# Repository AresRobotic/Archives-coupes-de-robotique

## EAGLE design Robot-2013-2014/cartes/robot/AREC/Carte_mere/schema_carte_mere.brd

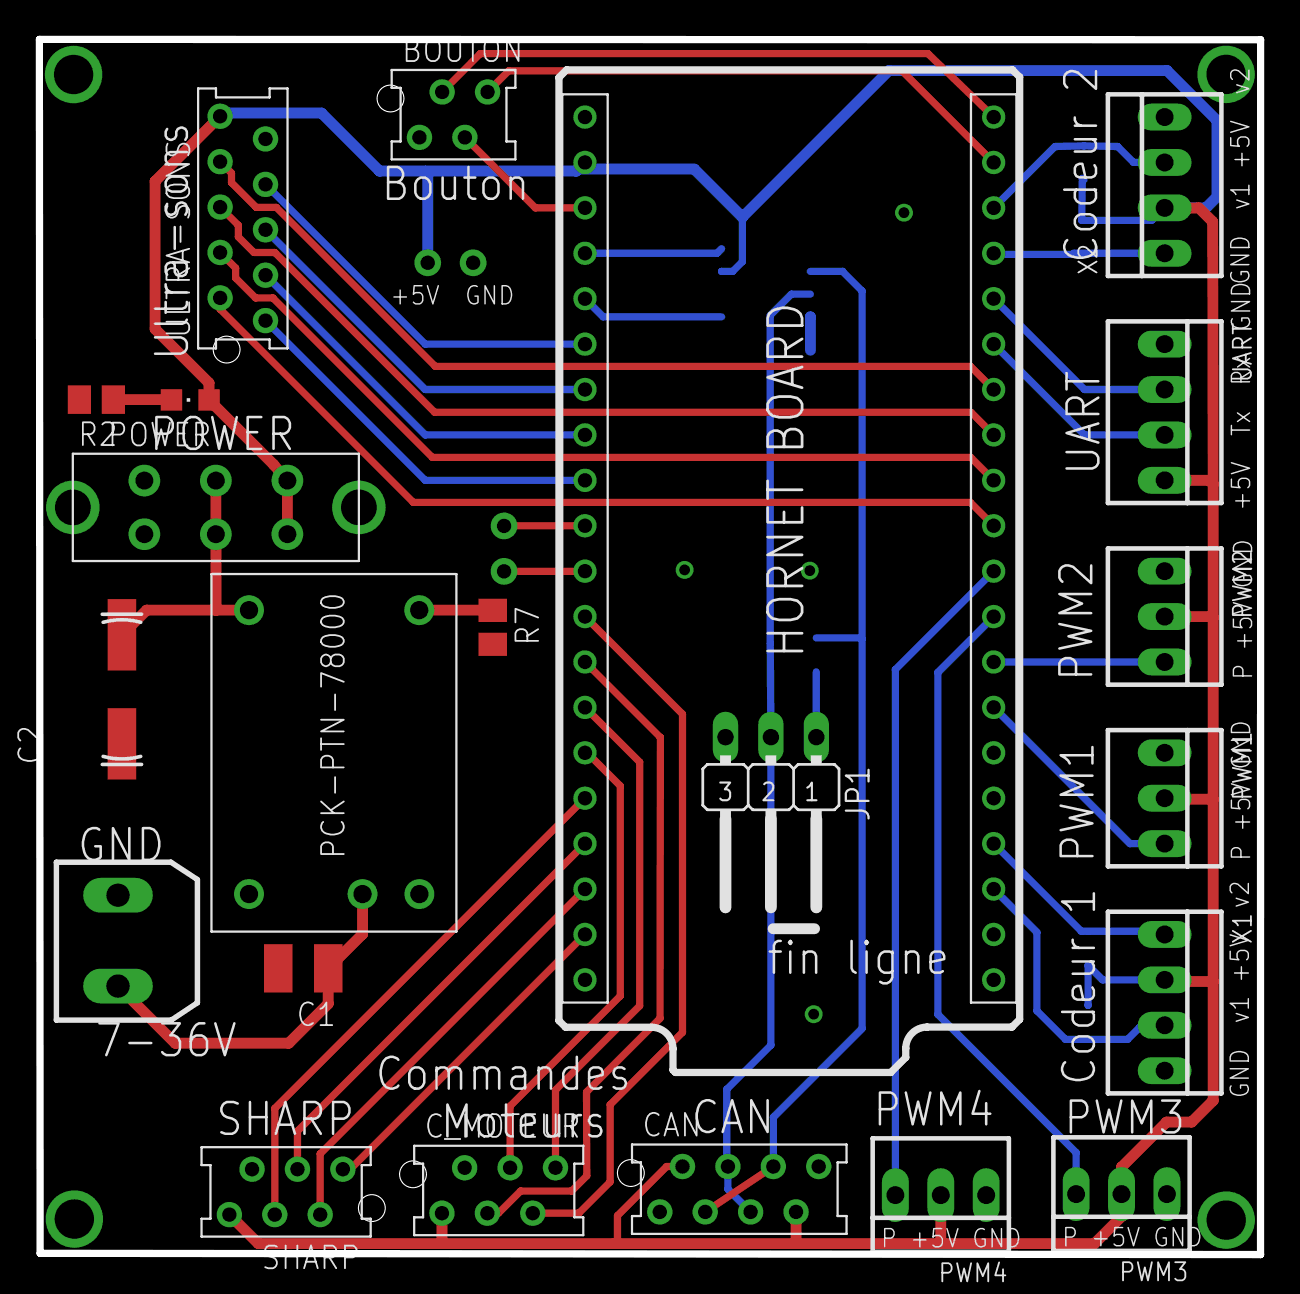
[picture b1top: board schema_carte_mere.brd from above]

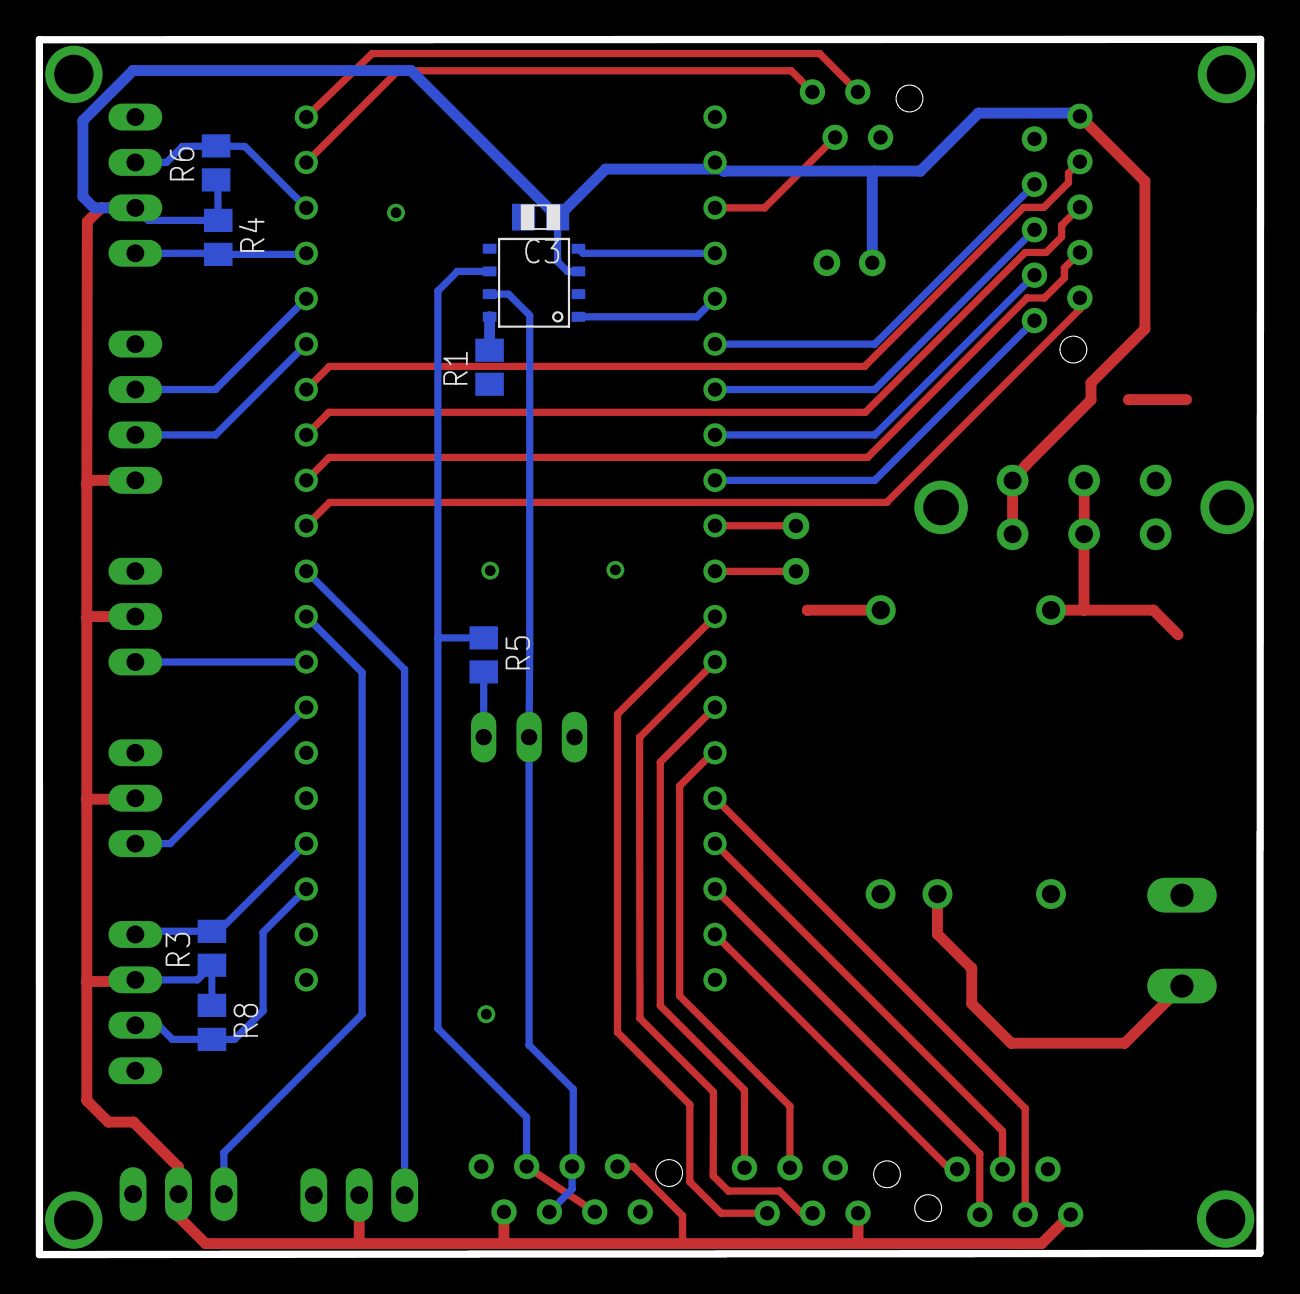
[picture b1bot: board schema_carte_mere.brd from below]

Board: 2 copper layers, 68.3 x 68.0 mm, 32 parts (8 on the bottom side), 43 nets.

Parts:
ALIM: PM5.08_2
BOUTON: MMATCH-4-; AMP-215079-4
C1: 2.2u; C1210
C2: 100uF; 153CLV-0807
C3: 100nF; C0805
CAN: AMP-215079-8
C_MOTEUR: MMATCH-6-; AMP-215079-6
JP1: JP2W
PIN_ALIM: 2_PIN
POWER: CHIPLED_0805
PWM1, PWM2, PWM3, PWM4: 22-23-2031
R1, R7: 21k; M0805
R2: 1k; M0805
R3, R4, R6, R8: 2.7k; M0805
R5: 120; M0805
SHARP: MMATCH-6-; AMP-215079-6
U$1: HORNET_BOARD; HORNET_EXT_20
U$2: MCP2551; SOIC_8
U$3: 2_PIN
U$6: SWITCH
U$18: PTN-78000WAH; PCK-PTN-78000WAH
UART: 22-23-2041
ULTRA-SONS: AMP-215079-10
X1, X2: 22-23-2041

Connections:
+3V3: BOUTON.3, U$1.P$3
+5V: C3.1, CAN.2, CAN.7, C_MOTEUR.1, PIN_ALIM.P$1, POWER.A, PWM1.2, PWM2.2, PWM3.2, PWM4.2, R3.1, R4.1, R6.1, R8.1, SHARP.6, U$1.P$2, U$2.P3, U$6.3, U$6.6, UART.4, ULTRA-SONS.10, X1.2, X2.2
CANH: CAN.4, CAN.5, JP1.2, U$2.P7
CANL: CAN.3, CAN.6, R5.1, U$2.P6
CANRX: U$1.P$4, U$2.P4
CANTX: U$1.P$5, U$2.P1
CODEUR1_V1: R8.2, U$1.P$23, X1.3
CODEUR1_V2: R3.2, U$1.P$24, X1.1
CODEUR2_V1: R4.2, U$1.P$37, X2.1
CODEUR2_V2: R6.2, U$1.P$38, X2.3
COULEUR: BOUTON.4, U$1.P$39
DIR1: C_MOTEUR.3, U$1.P$13
DIR2: C_MOTEUR.5, U$1.P$12
E1: U$1.P$6, ULTRA-SONS.7
E2: U$1.P$7, ULTRA-SONS.5
E3: U$1.P$8, ULTRA-SONS.3
E4: U$1.P$9, ULTRA-SONS.1
GND: ALIM.P$2, BOUTON.1, C1.2, C2.-, C3.2, CAN.1, CAN.8, C_MOTEUR.2, PIN_ALIM.P$2, PWM1.1, PWM2.1, PWM3.1, PWM4.1, R1.1, R2.2, R7.2, SHARP.5, U$1.P$1, U$2.P2, U$18.1, UART.1, ULTRA-SONS.9, X1.4, X2.4
unnamed: ALIM.P$1, C1.1, U$18.2
unnamed: POWER.C, R2.1
unnamed: R1.2, U$2.P8
unnamed: C2.+, U$6.2, U$6.5, U$18.5
unnamed: U$1.P$11, U$3.P$1
unnamed: R7.1, U$18.4
unnamed: JP1.1, R5.2
unnamed: U$1.P$10, U$3.P$2
PWM1: PWM1.3, U$1.P$27
PWM2: PWM2.3, U$1.P$28
PWM3: PWM3.3, U$1.P$29
PWM4: PWM4.3, U$1.P$30
PWM_MOT1: C_MOTEUR.4, U$1.P$15
PWM_MOT2: C_MOTEUR.6, U$1.P$14
SHARP1: SHARP.4, U$1.P$16
SHARP2: SHARP.3, U$1.P$17
SHARP3: SHARP.2, U$1.P$18
SHARP4: SHARP.1, U$1.P$19
T1: U$1.P$34, ULTRA-SONS.8
T2: U$1.P$33, ULTRA-SONS.6
T3: U$1.P$32, ULTRA-SONS.4
T4: U$1.P$31, ULTRA-SONS.2
TIRETTE: BOUTON.2, U$1.P$40
UART_RX: U$1.P$36, UART.2
UART_TX: U$1.P$35, UART.3

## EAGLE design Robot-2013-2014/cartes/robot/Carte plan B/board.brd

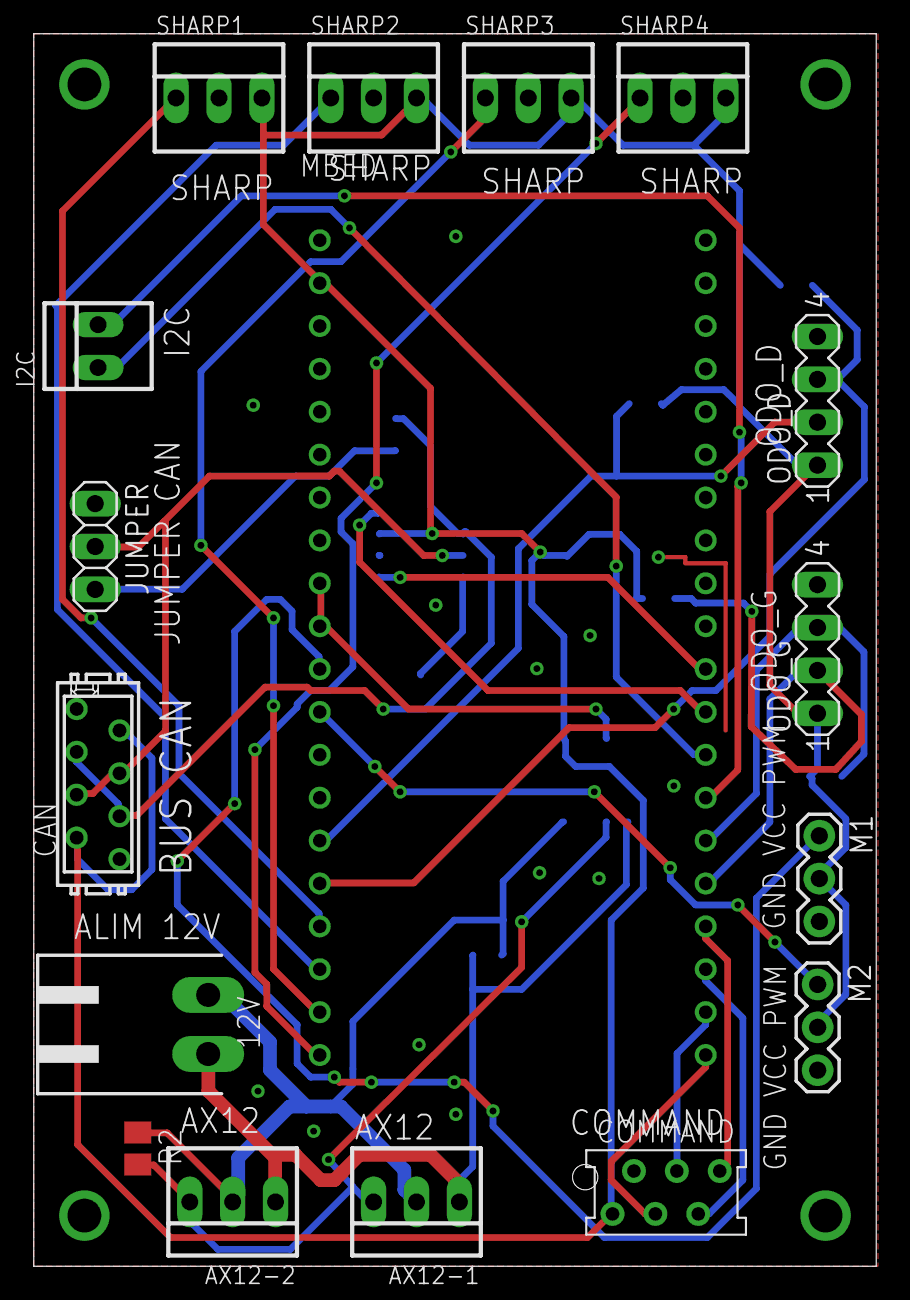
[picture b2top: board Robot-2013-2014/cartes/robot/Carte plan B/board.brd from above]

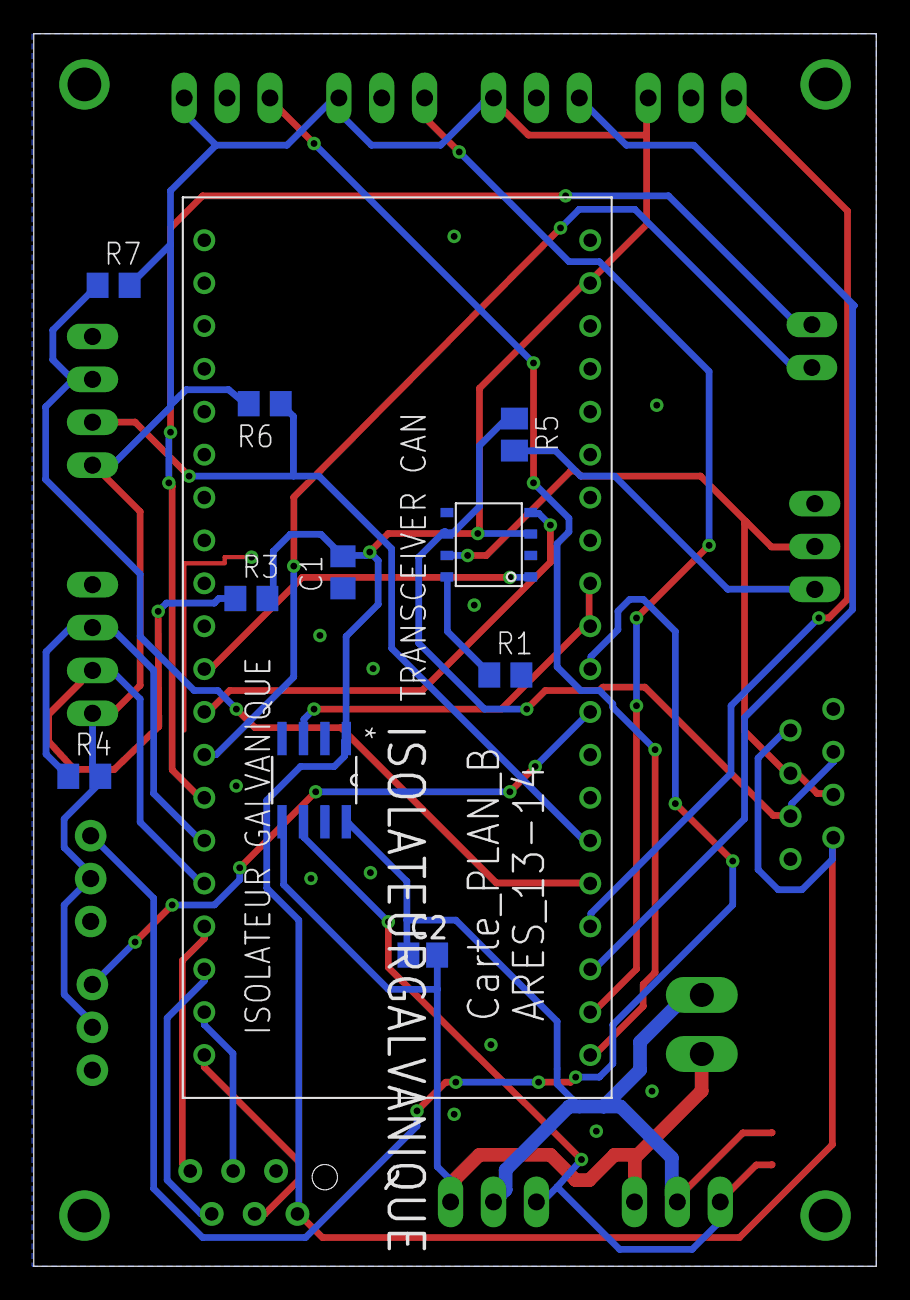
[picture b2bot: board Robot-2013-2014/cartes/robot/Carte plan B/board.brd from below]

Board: 2 copper layers, 49.9 x 73.0 mm, 27 parts (10 on the bottom side), 28 nets.

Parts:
12V: WEIDMULLER 2; 90G-2
AX12-1, AX12-2: molex-3; 22-23-2031
C1: 100n; C0805
C2: 100u; 0805
CAN: micromatch-8; MICROMATCH-8
COMMAND: MMATCH-6-; AMP-215079-6
I2C: header-2; 22-23-2021
ISOLATEURGALVANIQUE: ADUM1250ARZ; SOIC127P600X175-8N
JUMPER: 1X03
M1, M2: SMALL_SERVO; 1X03
MBED: MBED_NXP_LPC1768; MBED-KIT
ODO_D: header-4; MA04-1
ODO_G: header-4; MA04-1
R1: 21k; R0805
R2, R5: 120; M0805
R3, R4, R6, R7: 2,7k; R0805
SHARP1, SHARP2, SHARP3, SHARP4: header-3; 22-23-2031
TRANSCEIVER: MCP2551; SOIC_8

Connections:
+5V: C1.2, CAN.2, CAN.7, COMMAND.1, ISOLATEURGALVANIQUE.1, M1.2, M2.2, MBED.VIN, ODO_D.1, ODO_G.1, R3.2, R4.2, R6.2, R7.2, SHARP1.3, SHARP2.3, SHARP3.3, SHARP4.3, TRANSCEIVER.P3
+12V_DIRTY: 12V.1, AX12-1.2, AX12-2.2, C2.1, ISOLATEURGALVANIQUE.8, R2.1
CANH: CAN.4, CAN.5, JUMPER.2, TRANSCEIVER.P7
CANL: CAN.3, CAN.6, R5.1, TRANSCEIVER.P6
CAN_RX: MBED.P$29, TRANSCEIVER.P4
CAN_TX: MBED.P$30, TRANSCEIVER.P1
CHA_D: MBED.P$15, ODO_D.2, R6.1
CHA_G: MBED.P$25, ODO_G.2, R3.1
CHB_D: MBED.P$16, ODO_D.3, R7.1
CHB_G: MBED.P$26, ODO_G.3, R4.1
DATA_AX12: ISOLATEURGALVANIQUE.3, MBED.P$9, MBED.P$10
DATA_AX12_DIRTY: AX12-1.3, AX12-2.3, ISOLATEURGALVANIQUE.6, R2.2
DATA_SHARP_1: MBED.P$17, SHARP1.1
DATA_SHARP_2: MBED.P$18, SHARP2.1
DATA_SHARP_3: MBED.P$19, SHARP3.1
DATA_SHARP_4: MBED.P$20, SHARP4.1
DIR1: COMMAND.3, MBED.P$21
DIR2: COMMAND.5, MBED.P$23
GND: C1.1, CAN.1, CAN.8, COMMAND.2, ISOLATEURGALVANIQUE.4, M1.3, M2.3, MBED.GND, ODO_D.4, ODO_G.4, R1.2, SHARP1.2, SHARP2.2, SHARP3.2, SHARP4.2, TRANSCEIVER.P2
GND_DIRTY: 12V.2, AX12-1.1, AX12-2.1, C2.2, ISOLATEURGALVANIQUE.5
I2C_SCL: I2C.2, MBED.P$27
I2C_SDA: I2C.1, MBED.P$28
unnamed: R1.1, TRANSCEIVER.P8
unnamed: JUMPER.3, R5.2
PWM1: M1.1, MBED.P$11
PWM2: M2.1, MBED.P$12
PWM_MOT1: COMMAND.4, MBED.P$22
PWM_MOT2: COMMAND.6, MBED.P$24

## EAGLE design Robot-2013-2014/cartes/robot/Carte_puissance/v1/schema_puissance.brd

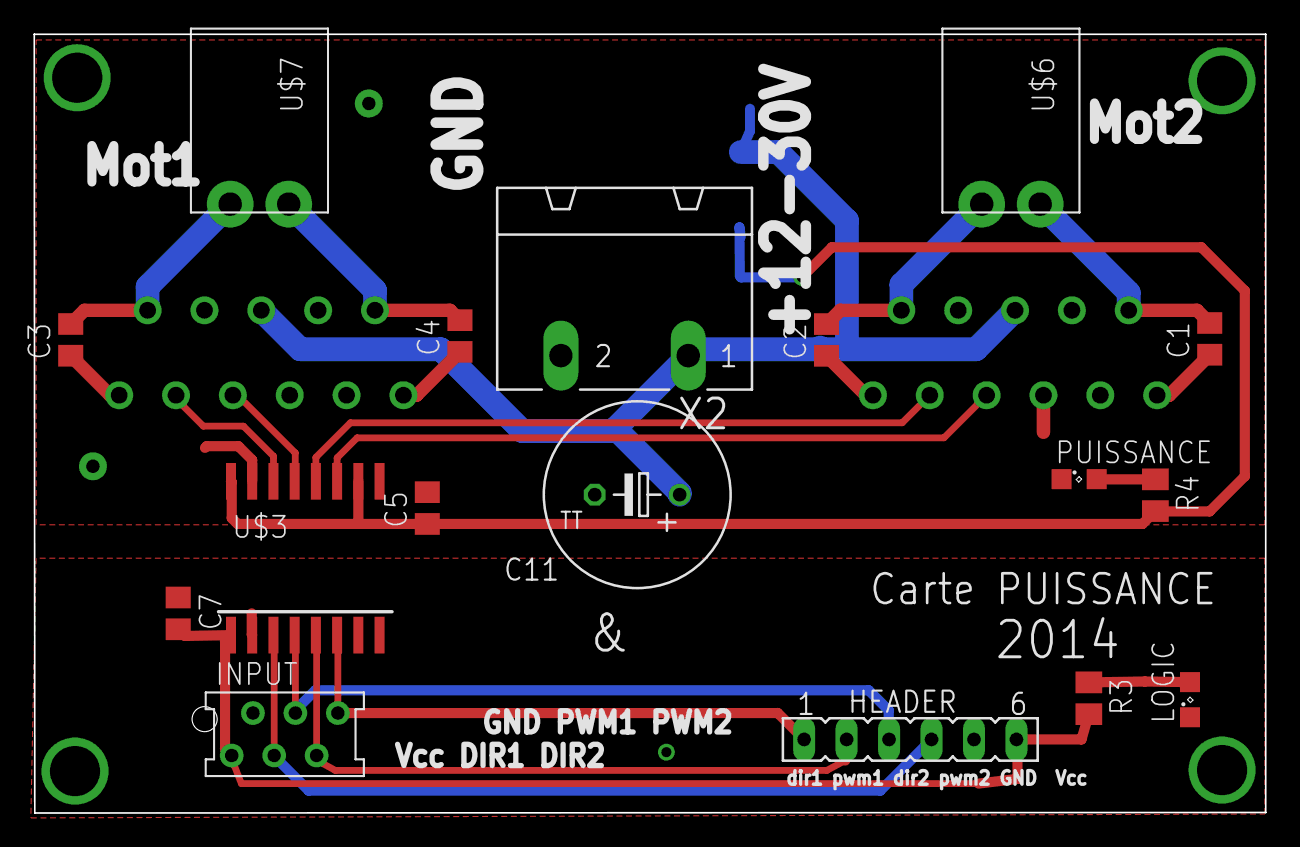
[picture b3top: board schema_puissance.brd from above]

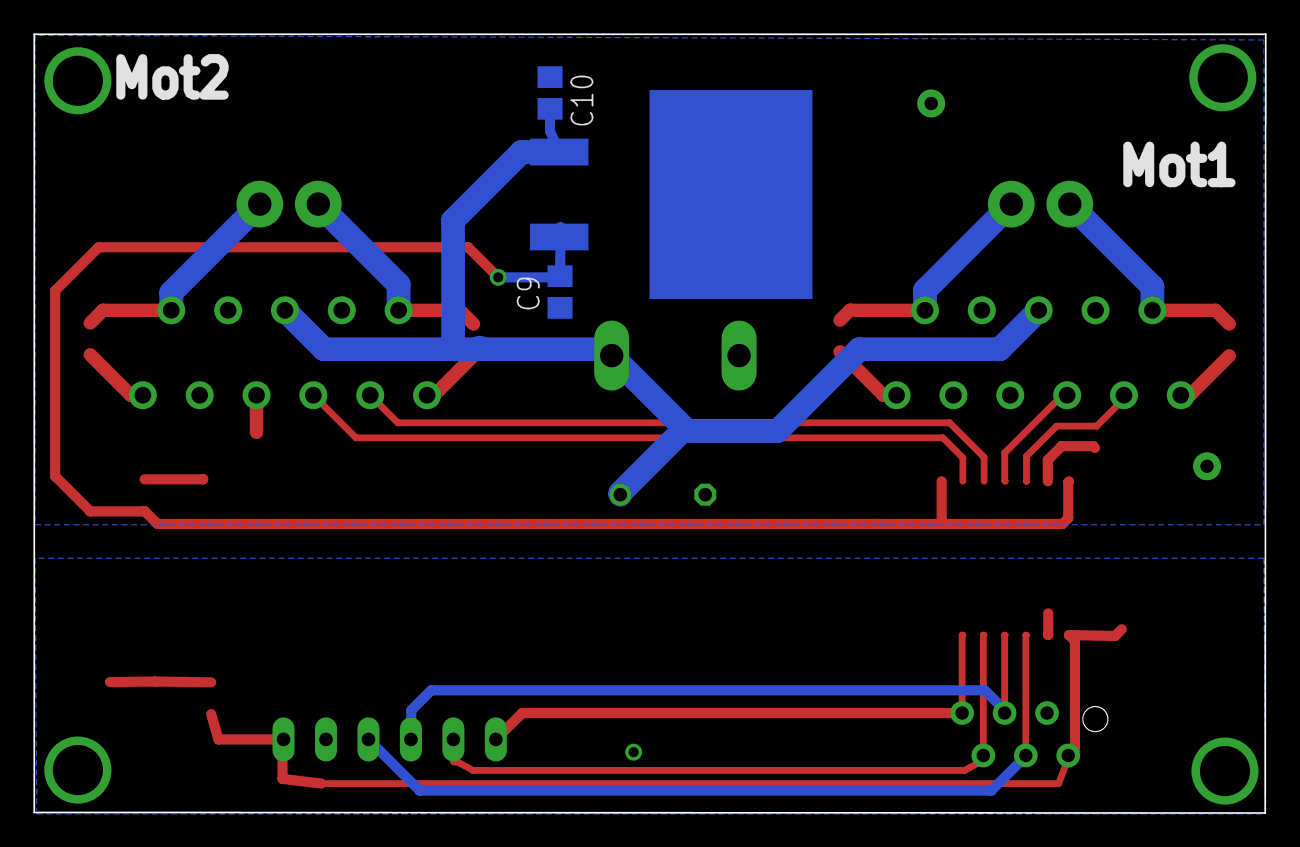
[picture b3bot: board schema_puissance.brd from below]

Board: 2 copper layers, 73.7 x 46.6 mm, 22 parts (3 on the bottom side), 23 nets.

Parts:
C1, C2, C3, C4: 10nF; C0805
C5, C7, C9: 100nF; C0805
C10: 330nF; C0805
C11: 2200u; TT5D11
HEADER: FE06
INPUT: MMATCH-6-; AMP-215079-6
LOGIC: SML0805
PUISSANCE: SML0805
R3, R4: 1k; M0805
U$1, U$2: LMD18200
U$3: ADUM1400S; SO-16W
U$5: L7805TO263; DPAK
U$6, U$7: SL-3.5-2-90G
X2: GMSTBA2

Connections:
+5V: C5.1, C9.2, R4.2, U$3.10, U$3.16, U$5.3
+12V: C10.2, C11.+, U$1.6, U$2.6, U$5.2, X2.1
C_DIR1: HEADER.4, INPUT.3, U$3.3
C_DIR2: HEADER.2, INPUT.5, U$3.5
C_PWM1: HEADER.3, INPUT.4, U$3.4
C_PWM2: HEADER.1, INPUT.6, U$3.6
DIR1: U$1.3, U$3.14
DIR2: U$2.3, U$3.12
GND: C7.1, HEADER.5, INPUT.2, LOGIC.C, U$3.2, U$3.8
GNDA: C5.2, C9.1, C10.1, C11.-, PUISSANCE.C, U$1.4, U$1.7, U$2.4, U$2.7, U$3.9, U$3.15, U$5.1, X2.2
unnamed: C1.1, U$2.11
unnamed: PUISSANCE.A, R4.1
unnamed: C2.1, U$2.1
unnamed: LOGIC.A, R3.1
unnamed: C3.1, U$1.1
unnamed: C4.1, U$1.11
POLE_1_MOT1: C3.2, U$1.2, U$7.1
POLE_1_MOT2: C2.2, U$2.2, U$6.1
POLE_2_MOT1: C4.2, U$1.10, U$7.2
POLE_2_MOT2: C1.2, U$2.10, U$6.2
PWM1: U$1.5, U$3.13
PWM2: U$2.5, U$3.11
VCC: C7.2, HEADER.6, INPUT.1, R3.2, U$3.1

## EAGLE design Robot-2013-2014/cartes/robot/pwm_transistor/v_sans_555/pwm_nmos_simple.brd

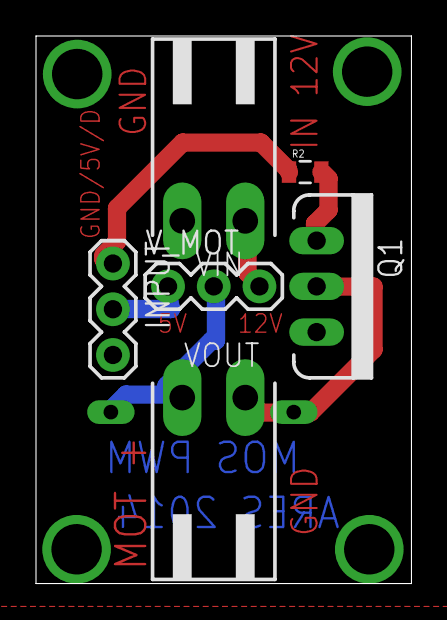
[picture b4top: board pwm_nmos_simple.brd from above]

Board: 2 copper layers, 20.9 x 30.4 mm, 7 parts (1 on the bottom side), 7 nets.

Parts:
D1: 1N821; DO35Z10
INPUT: 1X03
Q1: MOSFET-NCHANNELFQP30N06L; TO220V
R2: 10ohm; 0805
VIN: 90-2
VOUT: 90-2
V_MOT: 1X03

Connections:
12V: VIN.1, V_MOT.3
GND: INPUT.3, Q1.3, VIN.2
IN_MOS: INPUT.1, R2.1
unnamed: Q1.1, R2.2
V+_MOT: D1.C, VOUT.1, V_MOT.2
VCC: INPUT.2, V_MOT.1
VOUT: D1.A, Q1.2, VOUT.2

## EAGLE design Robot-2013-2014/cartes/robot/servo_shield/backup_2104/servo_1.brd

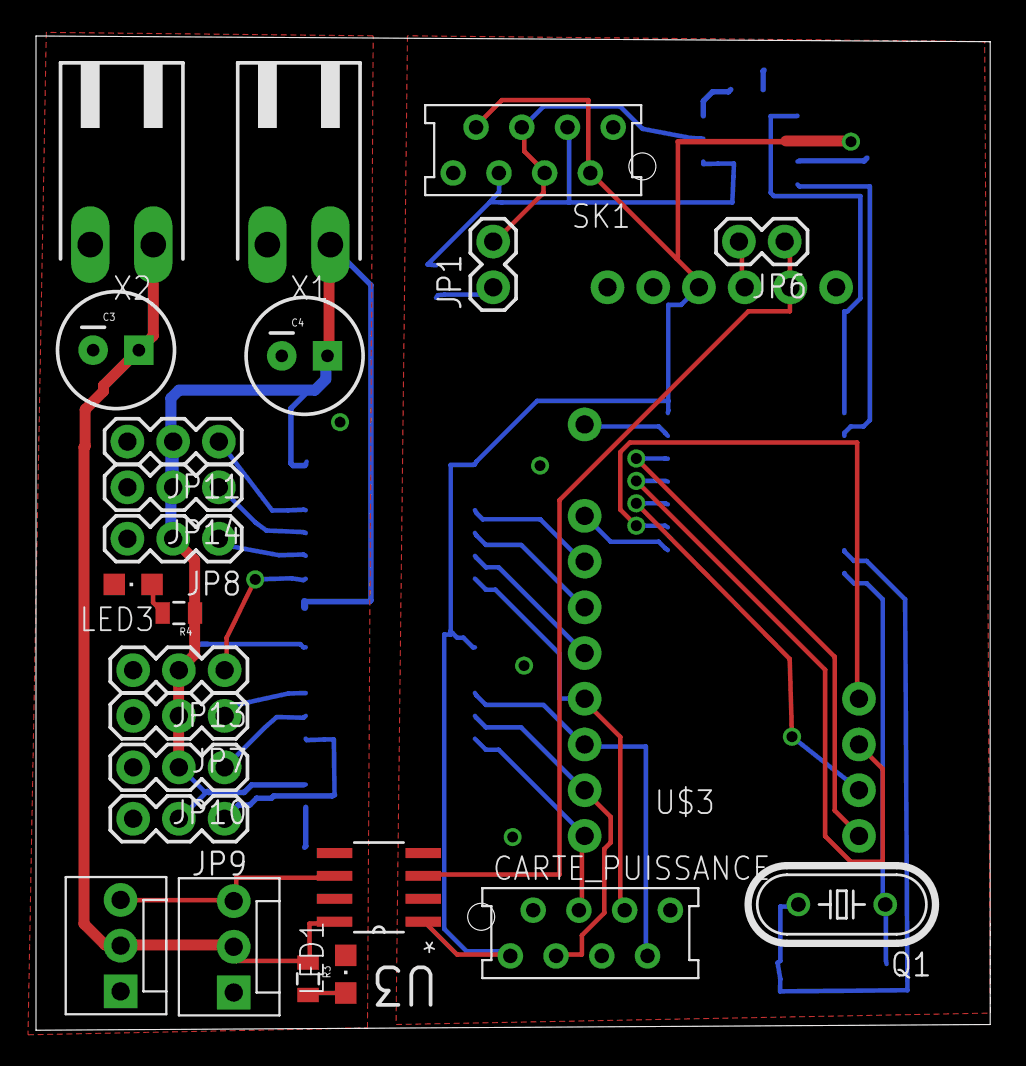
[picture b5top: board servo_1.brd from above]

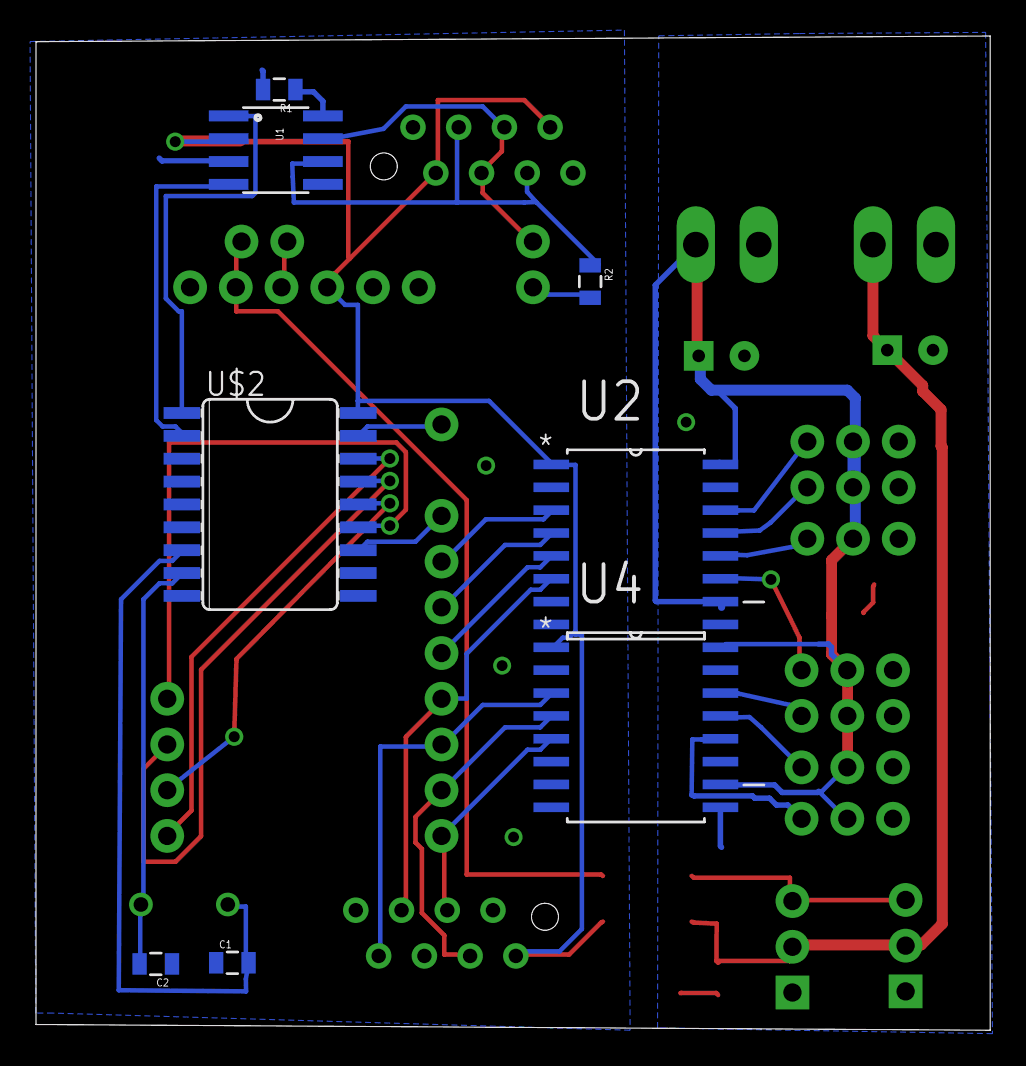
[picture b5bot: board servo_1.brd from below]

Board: 2 copper layers, 53.0 x 55.2 mm, 32 parts (8 on the bottom side), 38 nets.

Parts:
C1, C2: 22pF; 0805
C3, C4: 100uF; CPOL-RADIAL-100UF-25V
CARTE_PUISSANCE: AMP-215079-8
JP1: end_lign; 1X02
JP2: AX-12_1; MOLEX-1X3
JP4: AX-12_2; MOLEX-1X3
JP6: RX_TX_Connxion; 1X02
JP7: PWM7; 1X03
JP8: PWM5; 1X03
JP9: servo_option_2; 1X03
JP10: servo_option_1; 1X03
JP11: PWM3; 1X03
JP13: PWM6; 1X03
JP14: PWM4; 1X03
LED1, LED3: CHIPLED_0805
Q1: 16MHz; HC49/S
R1: 4,7k; 0805
R2: 120; 0805
R3, R4: 1k; 0805
SK1: AMP-215079-8
U1: MCP2551; SO08
U2, U4: ADUM1400ARWZ; SOIC127P1032X265-16N
U3: ADUM1250ARZ; SOIC127P600X175-8N
U$2: MCP2515SO; SO18L
U$3: ARDUINO_PRO_MINI'SERVO; ARDUINO_PRO_MINI
X1: 5V_INPUT; 90-2
X2: 12V_INPUT; 90-2

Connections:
5V_DIRTY: C4.1, JP7.2, JP8.2, JP9.2, JP10.2, JP11.2, JP13.2, JP14.2, R4.1, U2.10, U2.16, U4.10, U4.16, X1.1
12V_DIRTY: C3.1, JP2.2, JP4.2, R3.1, U3.8, X2.1
CANH: JP1.2, SK1.4, SK1.5, U1.7
CANL: R2.1, SK1.3, SK1.6, U1.6
CAN_CS: U$2.16, U$3.13
CAN_INT: U$2.12, U$3.5
CAN_RXD: U1.4, U$2.2
CAN_TXD: U1.1, U$2.1
GND: C1.1, C2.1, CARTE_PUISSANCE.2, R1.2, SK1.1, SK1.8, U1.3, U2.2, U2.8, U3.4, U4.2, U4.8, U$2.9, U$3.GND
GND_DIRTY: C3.2, C4.2, JP2.1, JP4.1, JP7.3, JP8.3, JP9.3, JP10.3, JP11.3, JP13.3, JP14.3, LED1.C, LED3.C, U2.9, U2.15, U3.5, U4.9, U4.15, X1.2, X2.2
MISO: U$2.15, U$3.15
MOSI: U$2.14, U$3.14
unnamed: C1.2, Q1.2, U$2.7
unnamed: C2.2, Q1.1, U$2.8
unnamed: LED1.A, R3.2
unnamed: R1.1, U1.8
unnamed: LED3.A, R4.2
unnamed: JP1.1, R2.2
PWM3: U2.3, U$3.6
PWM3_OUT: JP11.1, U2.14
PWM4: U2.4, U$3.7
PWM4_OUT: JP14.1, U2.13
PWM5: U2.5, U$3.8
PWM5_OUT: JP8.1, U2.12
PWM6: CARTE_PUISSANCE.6, U2.6, U$3.9
PWM6_OUT: JP13.1, U2.11
PWM7: CARTE_PUISSANCE.7, U4.3, U$3.10
PWM7_OUT: JP7.1, U4.14
PWM8: CARTE_PUISSANCE.3, U4.4, U$3.11
PWM8_OUT: JP10.1, U4.13
PWM9: CARTE_PUISSANCE.4, U4.5, U$3.12
PWM9_OUT: JP9.1, U4.12
RST: U$2.17, U$3.3
RXI: JP6.2, U$3.RXI
RXTX_OUT: JP2.3, JP4.3, U3.6
SCK: U$2.13, U$3.16
TXO: JP6.1, U3.3, U$3.TXO
VCC: CARTE_PUISSANCE.1, SK1.2, SK1.7, U1.2, U2.1, U3.1, U4.1, U$2.18, U$3.VCC

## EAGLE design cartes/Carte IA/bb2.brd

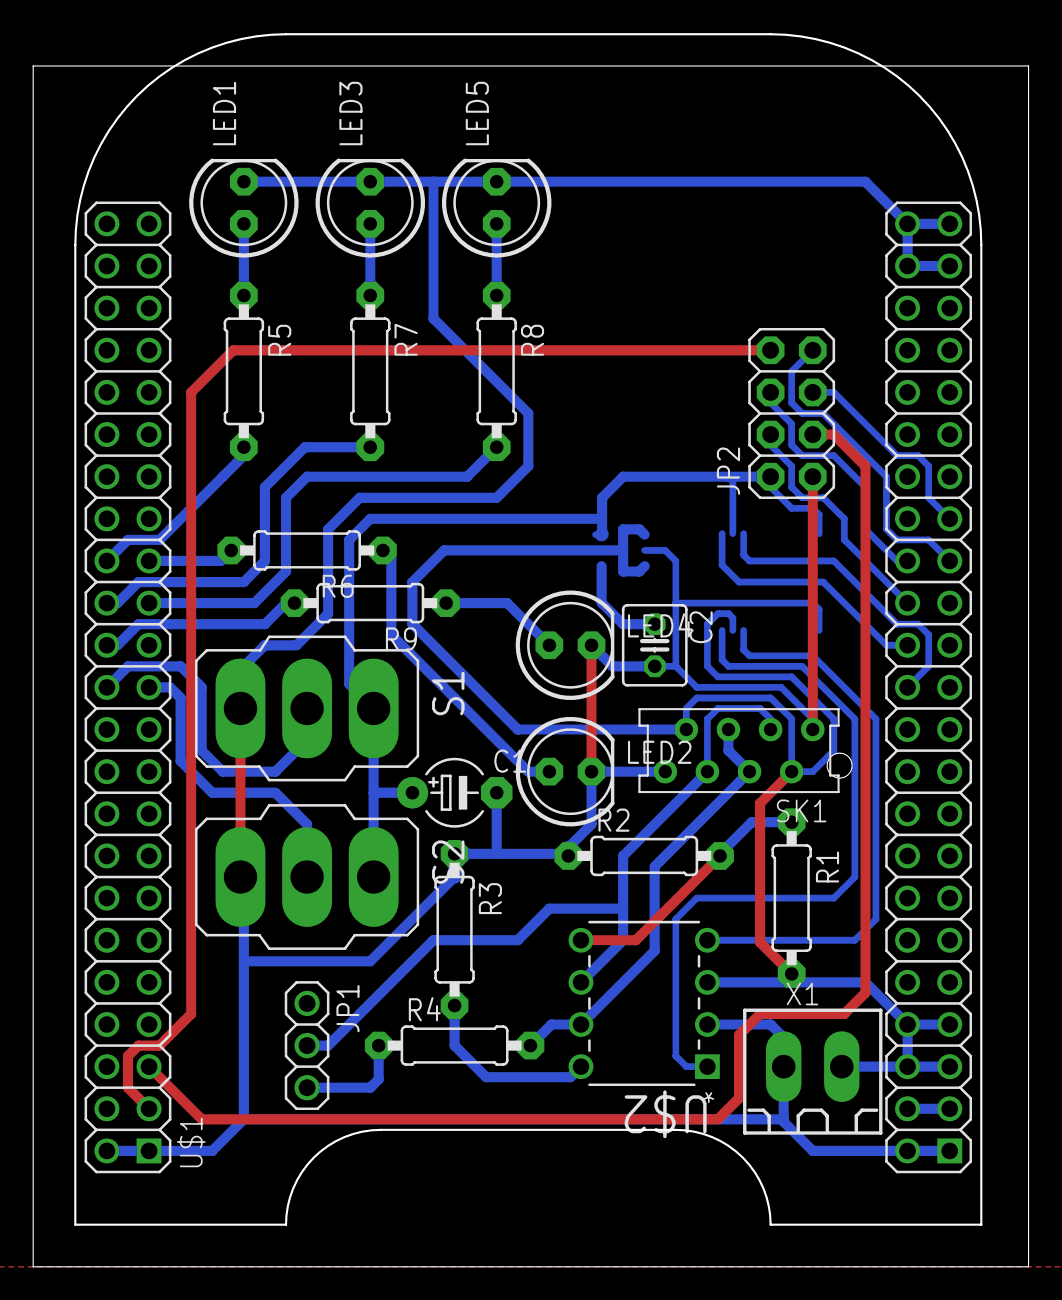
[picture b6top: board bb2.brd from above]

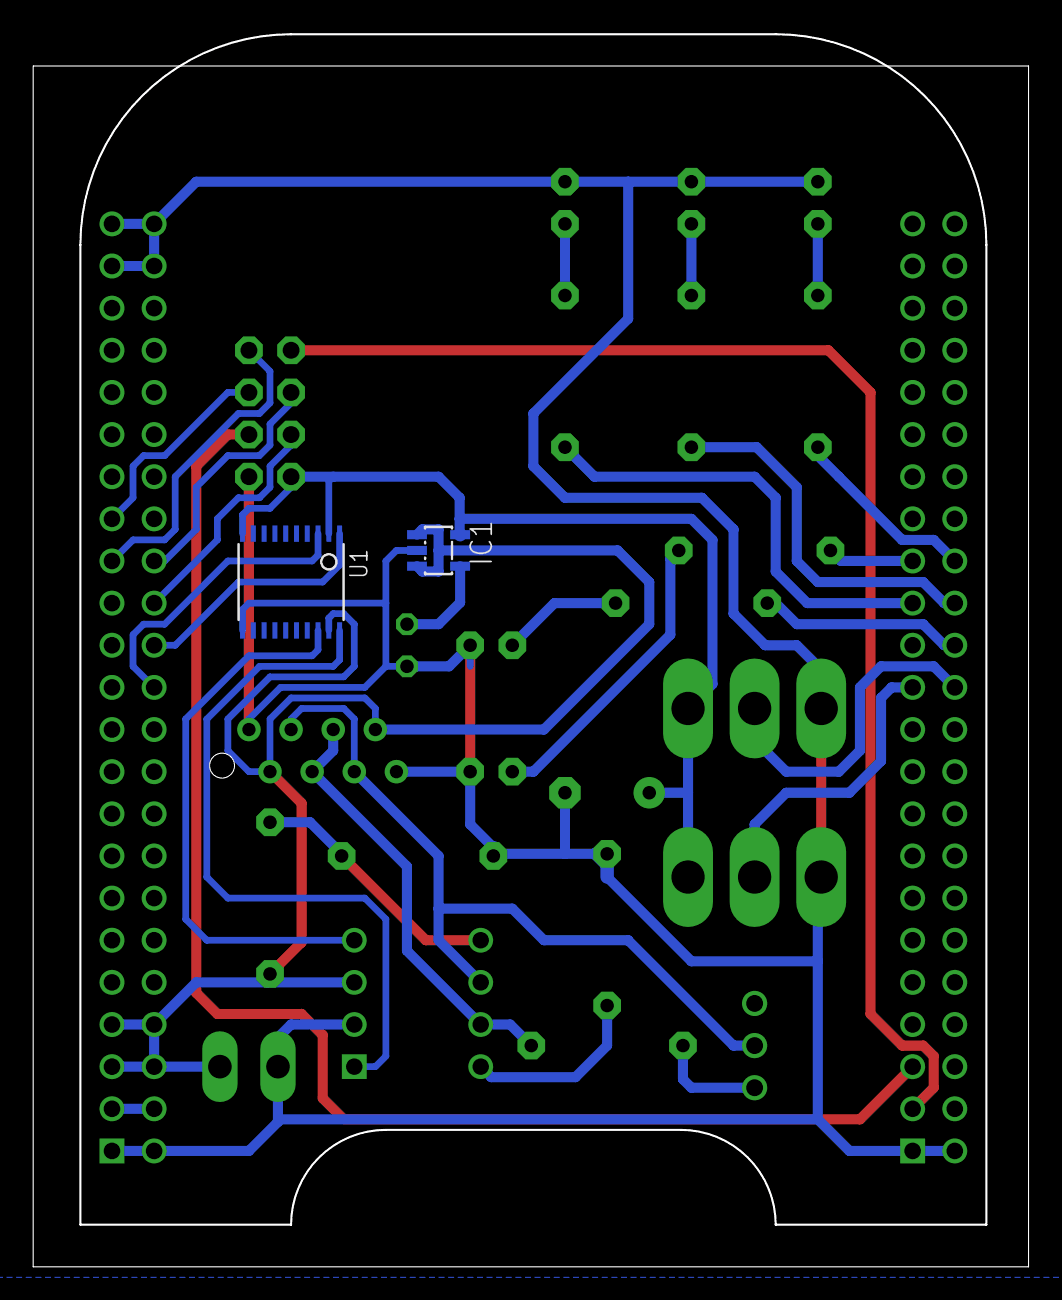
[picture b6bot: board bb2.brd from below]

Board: 2 copper layers, 60.0 x 74.3 mm, 26 parts (2 on the bottom side), 32 nets.

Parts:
C1: 2.2u; E5-4
C2: 470p; C025-040X050
IC1: MIC5219BM5; SOT23-5
JP1: 1X03
JP2: 2X04
LED1, LED2, LED3, LED4, LED5: LED5MM
R1, R2, R5, R6, R7, R8, R9: 47k; 0207/9
R3: 4.7k; 0207/9
R4: 120; 0207/9
S1, S2: 320-916
SK1: AMP-215079-8
U1: TSSOP20
U$1: BEAGLEBONE_OUTLINE; BEAGLEBONE_SHIELD
U$2: MCP2551-E/P; DIP254P762X432-8
X1: 180G-2

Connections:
DCAN1_RX: U1.3, U$1.70
DCAN1_TX: U1.1, U$1.72
GND: C1.-, C2.2, IC1.2, JP2.1, LED1.K, LED2.K, LED3.K, LED4.K, LED5.K, R2.1, R3.1, S1.3, S2.3, SK1.1, SK1.8, U1.11, U$1.1, U$1.2, U$1.47, U$1.48, U$1.89, U$1.90, U$1.91, U$1.92, U$2.2, X1.1
unnamed: R1.1, R2.2, U$2.5
unnamed: JP1.3, R4.1
unnamed: R3.2, U$2.8
unnamed: C2.1, IC1.4
unnamed: R5.2, U$1.30
unnamed: R6.2, U$1.29
unnamed: R7.2, U$1.28
unnamed: R9.2, U$1.26
unnamed: LED5.A, R8.1
unnamed: S1.2, U$1.24
unnamed: S2.2, U$1.23
unnamed: R8.2, U$1.27
unnamed: JP1.2, SK1.3, SK1.6, U$2.6
unnamed: R4.2, SK1.4, SK1.5, U$2.7
unnamed: LED2.A, R6.1
unnamed: LED1.A, R5.1
unnamed: LED3.A, R7.1
unnamed: LED4.A, R9.1
RXD: U1.18, U$2.4
SPI_CE: JP2.3, U$1.5
SPI_CS: JP2.4, U$1.74
SPI_IRQ: JP2.8, U$1.3
SPI_MISO: JP2.7, U$1.75
SPI_MOSI: JP2.6, U$1.76
SPI_SCLK: JP2.5, U$1.77
TXD: U1.20, U$2.1
VDD: IC1.1, IC1.3, R1.2, SK1.2, SK1.7, U1.19, U$1.51, U$1.52, U$1.53, U$1.54, U$2.3, X1.2
VDD_3V3: C1.+, IC1.5, JP2.2, S1.1, S2.1, U1.2, U1.10
VDD_3V3EXP: U$1.49, U$1.50

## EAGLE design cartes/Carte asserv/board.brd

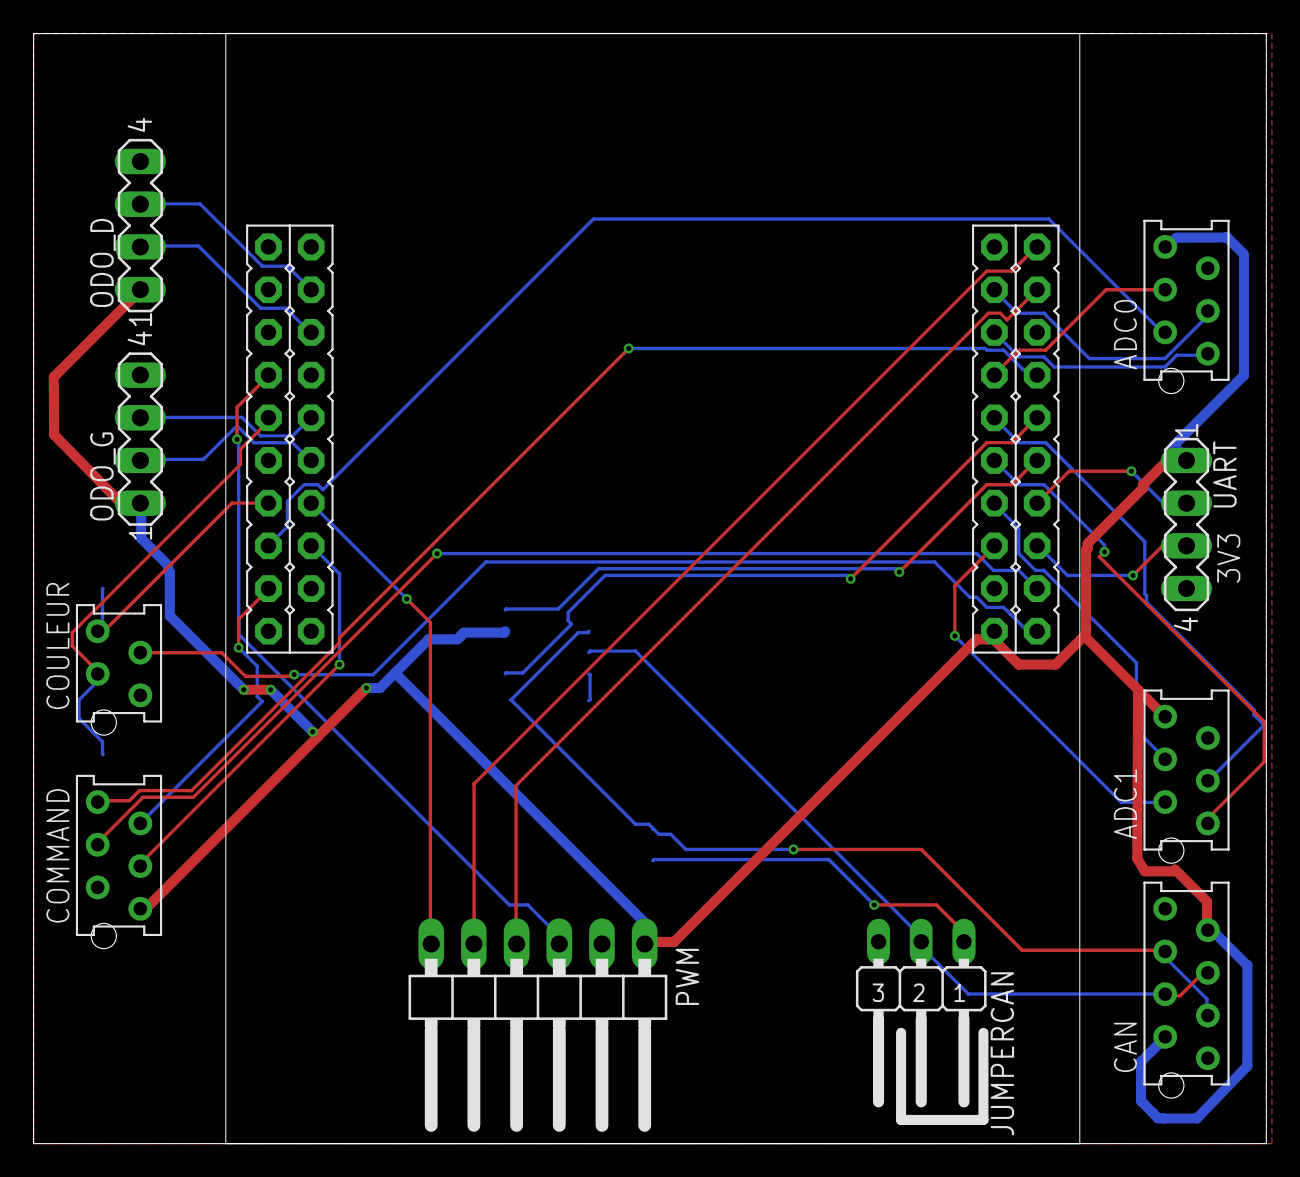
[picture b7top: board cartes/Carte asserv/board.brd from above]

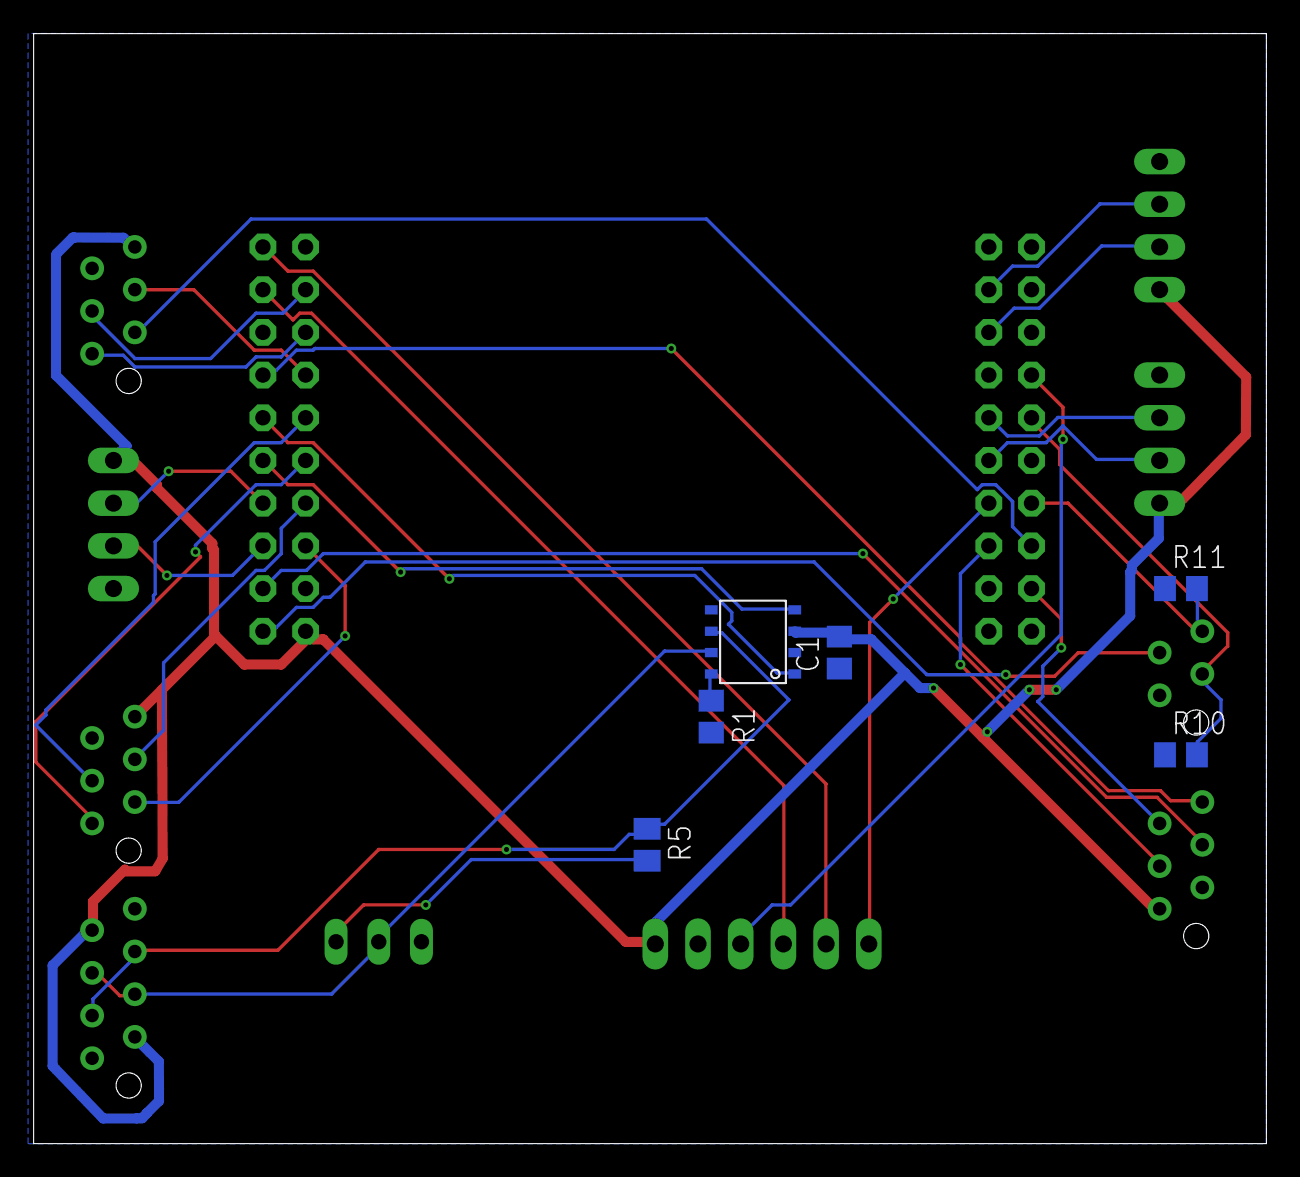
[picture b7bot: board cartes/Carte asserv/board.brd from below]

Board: 2 copper layers, 73.3 x 66.0 mm, 17 parts (6 on the bottom side), 33 nets.

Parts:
ADC0, ADC1: MMATCH-6-; AMP-215079-6
C1: 100n; C0805
CAN: AMP-215079-8
COMMAND: MMATCH-6-; AMP-215079-6
COULEUR: MMATCH-4-; AMP-215079-4
JUMPERCAN: JP2W
ODO_D: MA04-1
ODO_G: MA04-1
PWM: 1X06/90
R1: 21k; R0805
R5: 120; M0805
R10, R11: 10k; R0805
TIVA: STELLARIS-LAUNCHPADSTELLARIS-LAUNCHPAD; LAUNCHPAD-XL
U$1: MCP2551; SOIC_8
UART: MA04-1

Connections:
+5V: ADC0.6, ADC1.6, C1.2, CAN.2, CAN.7, COMMAND.1, ODO_D.1, ODO_G.1, PWM.1, TIVA.VBUS, U$1.P3, UART.1
ADC_0: ADC0.3, TIVA.PE3
ADC_1: ADC0.1, TIVA.PE2
ADC_2: ADC0.4, TIVA.PE1
ADC_3: ADC0.2, TIVA.PE0
ADC_4: ADC1.3, TIVA.PD3
ADC_5: ADC1.1, TIVA.PD2
ADC_6: ADC1.4, TIVA.PD1
ADC_7: ADC1.2, TIVA.PD0
CANH: CAN.4, CAN.5, JUMPERCAN.2, U$1.P7
CANL: CAN.3, CAN.6, R5.1, U$1.P6
CAN_RX: TIVA.PE4, U$1.P4
CAN_TX: TIVA.PE5, U$1.P1
CHA_D: ODO_D.2, TIVA.PD6
CHA_G: ODO_G.2, TIVA.PC5
CHB_D: ODO_D.3, TIVA.PD7
CHB_G: ODO_G.3, TIVA.PC6
COULEUR: COULEUR.4, R11.2, TIVA.PF0
DIR1: COMMAND.3, TIVA.PB3
DIR2: COMMAND.5, TIVA.PB2
GND: ADC0.5, ADC1.5, C1.1, CAN.1, CAN.8, COMMAND.2, COULEUR.1, ODO_D.4, ODO_G.4, PWM.2, R1.2, R10.1, R11.1, TIVA.GND1, TIVA.GND2, U$1.P2, UART.4
unnamed: R1.1, U$1.P8
unnamed: JUMPERCAN.1, R5.2
PWM1: PWM.3, TIVA.PB6
PWM2: PWM.4, TIVA.PA6
PWM3: PWM.5, TIVA.PA7
PWM4: PWM.6, TIVA.PC4
PWM_MOT1: COMMAND.4, TIVA.PB5
PWM_MOT2: COMMAND.6, TIVA.PB4
TIRETTE: COULEUR.2, R10.2, TIVA.PB7
UART_RX: TIVA.PB0, UART.3
UART_TX: TIVA.PB1, UART.2
VDD_3V3: COULEUR.3, TIVA.3.3V

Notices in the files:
parts and their libraries:
SparkFun-Electromechanical: Licensing: CC v3.0 Share-Alike You are welcome to use this library for commercial purposes.
